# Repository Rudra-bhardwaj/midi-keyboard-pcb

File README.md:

# midi keyboard
midi keyboard is a musical synthesizer which is an electronic musical instrument that generates and modifies audio signals to create unique sounds

 ## features
1)EC11 Rotary Encoders

2)SK6812 MINI-E Neopixels

3)Bourns Slide Potentiometers

4)Kailh Choc Low-Profile Switches

5)and some copper pads to play music!

## BOM (bill of materials)
 | Designator    | Footprint                                      | Quantity | Value                    | Total Cost | Part                                                                                                                                                                                                                                                                                                                                                                                                                                                                                                                                                                                                                                                                                                |
|---------------|------------------------------------------------|----------|--------------------------|------------|-----------------------------------------------------------------------------------------------------------------------------------------------------------------------------------------------------------------------------------------------------------------------------------------------------------------------------------------------------------------------------------------------------------------------------------------------------------------------------------------------------------------------------------------------------------------------------------------------------------------------------------------------------------------------------------------------------|
| D1, D2, D3    | LED_SK6812MINI-E_3.2x2.8mm_P1.5mm_ReverseMount | 3        | SK6812MINI-E             | $3.36      | https://www.aliexpress.us/item/3256807677321116.html?spm=a2g0o.productlist.main.7.607a1c3clvX5x9&algo_pvid=bee2faba-4c6b-4fa4-89c4-5ca66e556568&algo_exp_id=bee2faba-4c6b-4fa4-89c4-5ca66e556568-6&pdp_ext_f=%7B%22order%22%3A%22643%22%2C%22eval%22%3A%221%22%2C%22fromPage%22%3A%22search%22%7D&pdp_npi=6%40dis%21CAD%215.30%214.88%21%21%213.65%213.36%21%402101e81117919481938394582e0f6e%2112000042594617264%21sea%21US%213725344934%21X%211%210%21n_tag%3A-29919%3Bd%3Ae2161723%3Bm03_new_user%3A-29895%3BpisId%3A5000000219770668&curPageLogUid=ehnx03TU7wEm&utparam-url=scene%3Asearch%7Cquery_from%3A%7Cx_object_id%3A1005007863635868%7C_p_origin_prod%3A                                 |
| J1            | Capacitive Keys                                | 1        | Capacitive Touch Buttons |            |                                                                                                                                                                                                                                                                                                                                                                                                                                                                                                                                                                                                                                                                                                     |
| RV1, RV2      | Potentiometer_Bourns_PTA1543_Single_Slide      | 2        | Slider                   | $3.16      | https://www.digikey.com/en/products/detail/bourns-inc/PTA1543-2010CIB103/3781161                                                                                                                                                                                                                                                                                                                                                                                                                                                                                                                                                                                                                    |
| SW1, SW2, SW3 | Kailh Choc Low-Profile Switches                | 3        | SW_Push                  | $6.04      | https://www.aliexpress.com/item/1005008883418065.html?spm=a2g0o.productlist.main.1.13d14a7e068OmL&algo_pvid=4e5fe6cd-3562-4ef4-ac3e-085a2d4634fe&algo_exp_id=4e5fe6cd-3562-4ef4-ac3e-085a2d4634fe-0&pdp_ext_f=%7B%22order%22%3A%221475%22%2C%22spu_best_type%22%3A%22price%22%2C%22eval%22%3A%221%22%2C%22fromPage%22%3A%22search%22%7D&pdp_npi=6%40dis%21CAD%2111.40%212.38%21%21%217.81%211.63%21%402103128917919263557114360e0ebd%2112000047082945007%21sea%21CA%210%21ABX%211%210%21n_tag%3A-29910%3Bd%3A778dde27%3Bm03_new_user%3A-29895%3BpisId%3A5000000218640848&curPageLogUid=CXjsh9TOCyFt&utparam-url=scene%3Asearch%7Cquery_from%3A%7Cx_object_id%3A1005008883418065%7C_p_origin_prod%3A |
| SW4           | RotaryEncoder_Alps_EC11E-Switch_Vertical_H20mm | 1        | RotaryEncoder_Switch_MP  | $1.44      | https://www.aliexpress.us/item/3256807457768762.html?spm=a2g0o.productlist.main.1.52d22c6as0ZCnv&algo_pvid=9965a6c7-9d4c-44f9-a2d4-a43aa1b0ae45&algo_exp_id=9965a6c7-9d4c-44f9-a2d4-a43aa1b0ae45-0&pdp_ext_f=%7B%22order%22%3A%224739%22%2C%22eval%22%3A%221%22%2C%22fromPage%22%3A%22search%22%7D&pdp_npi=6%40dis%21USD%211.52%211.40%21%21%211.52%211.40%21%402101e7a317919489056767943e0e88%2112000041630839409%21sea%21US%213725344934%21X%211%210%21n_tag%3A-29919%3Bd%3A1bb91aa6%3Bm03_new_user%3A-29895%3BpisId%3A5000000219770668&curPageLogUid=AOe3dpbqRVrY&utparam-url=scene%3Asearch%7Cquery_from%3A%7Cx_object_id%3A1005007644083514%7C_p_origin_prod%3A                                |
| U1            | Waveshare ESP32-S3-Zero                        | 1        | Waveshare ESP32-S3-ZERO  | $6.62      | https://www.aliexpress.com/item/1005007004089798.html?src=google&gatewayAdapt=4itemAdapt                                                                                                                                                                                                                                                                                                                                                                                                                                                                                                                                                                                                            |
|               |                                                |          |                          |            |                                                                                                                                                                                                                                                                                                                                                                                                                                                                                                                                                                                                                                                                                                     |
|               |                                                |          | Total Aliexpress:        | $19.59     |                                                                                                                                                                                                                                                                                                                                                                                                                                                                                                                                                                                                                                                                                                     |
|               |                                                |          | Total Digikey:           | $12.35     |                                                                                                                                                                                                                                                                                                                                                                                                                                                                                                                                                                                                                                                                                                     |
|               |                                                |          | Total JLCPCB:            | $12.29     |                                                                                                                                                                                                                                                                                                                                                                                                                                                                                                                                                                                                                                                                                                     |
|               |                                                |          | Total:                   | $44.23     |                                                                                                                                                                                                                                                                                                                                                                                                                                                                                                                                                                                                                                                                                                     |

## Images of the project

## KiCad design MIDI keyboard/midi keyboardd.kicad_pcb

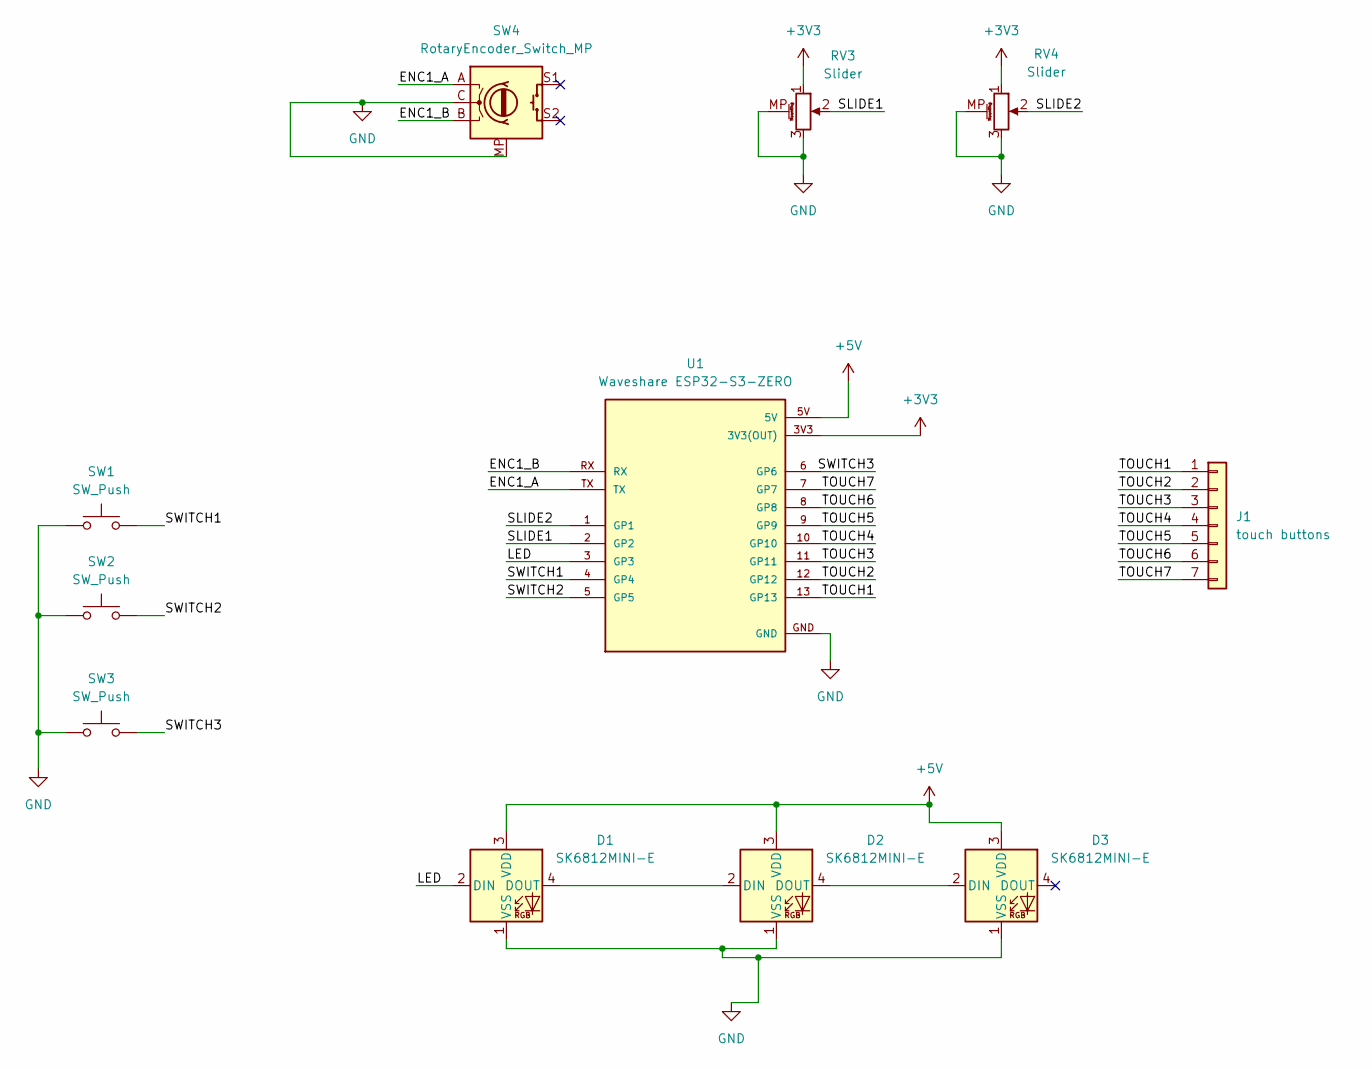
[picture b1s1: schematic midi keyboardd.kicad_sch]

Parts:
D1, D2, D3: SK6812MINI-E; LED_SK6812MINI-E_3.2x2.8mm_P1.5mm_ReverseMount
J1: touch buttons; touch pads
RV3, RV4: Slider; Potentiometer_Bourns_PTA1543_Single_Slide
SW1, SW2, SW3: SW_Push; Kailh Choc Low-Profile Switches
SW4: RotaryEncoder_Switch_MP; RotaryEncoder_Alps_EC11E-Switch_Vertical_H20mm
U1: Waveshare ESP32-S3-ZERO; Waveshare ESP32-S3-Zero; PARTREV NA

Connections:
+3V3: RV3.1, RV4.1, U1.3V3 (3V3(OUT))
+5V: D1.3 (VDD), D2.3 (VDD), D3.3 (VDD), U1.5V
/ENC1_A: SW4.A, U1.TX
/ENC1_B: SW4.B, U1.RX
/LED: D1.2 (DIN), U1.3 (GP3)
/SLIDE1: RV3.2, U1.2 (GP2)
/SLIDE2: RV4.2, U1.1 (GP1)
/SWITCH1: SW1.2, U1.4 (GP4)
/SWITCH2: SW2.2, U1.5 (GP5)
/SWITCH3: SW3.2, U1.6 (GP6)
/TOUCH1: J1.1, U1.13 (GP13)
/TOUCH2: J1.2, U1.12 (GP12)
/TOUCH3: J1.3, U1.11 (GP11)
/TOUCH4: J1.4, U1.10 (GP10)
/TOUCH5: J1.5, U1.9 (GP9)
/TOUCH6: J1.6, U1.8 (GP8)
/TOUCH7: J1.7, U1.7 (GP7)
GND: D1.1 (VSS), D2.1 (VSS), D3.1 (VSS), RV3.3, RV3.MP (MountPin), RV4.3, RV4.MP (MountPin), SW1.1, SW2.1, SW3.1, SW4.C, SW4.MP, U1.GND
unnamed: D1.4 (DOUT), D2.2 (DIN)
unnamed: D2.4 (DOUT), D3.2 (DIN)

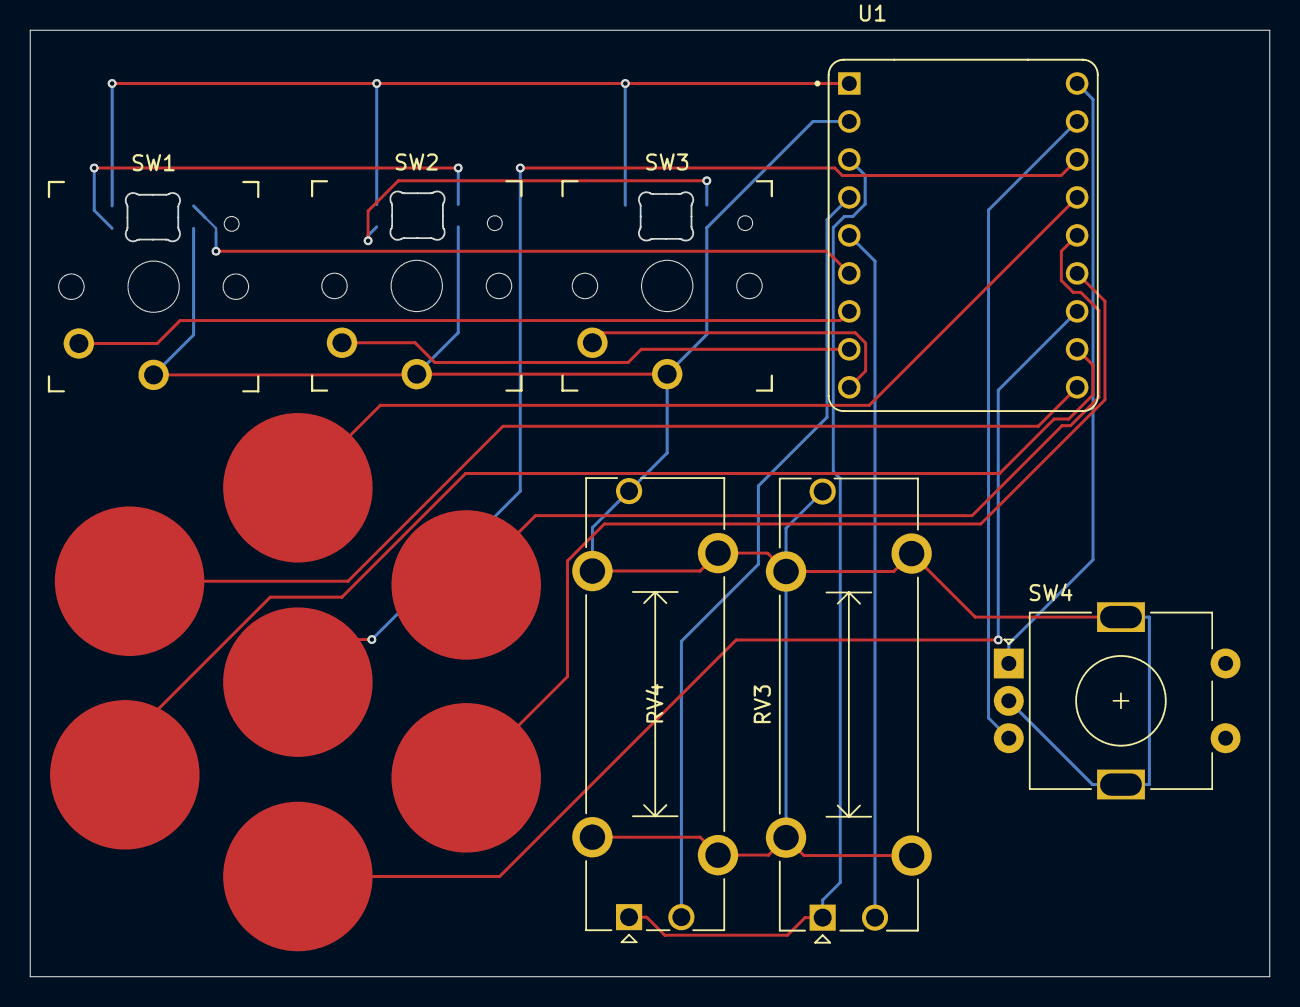
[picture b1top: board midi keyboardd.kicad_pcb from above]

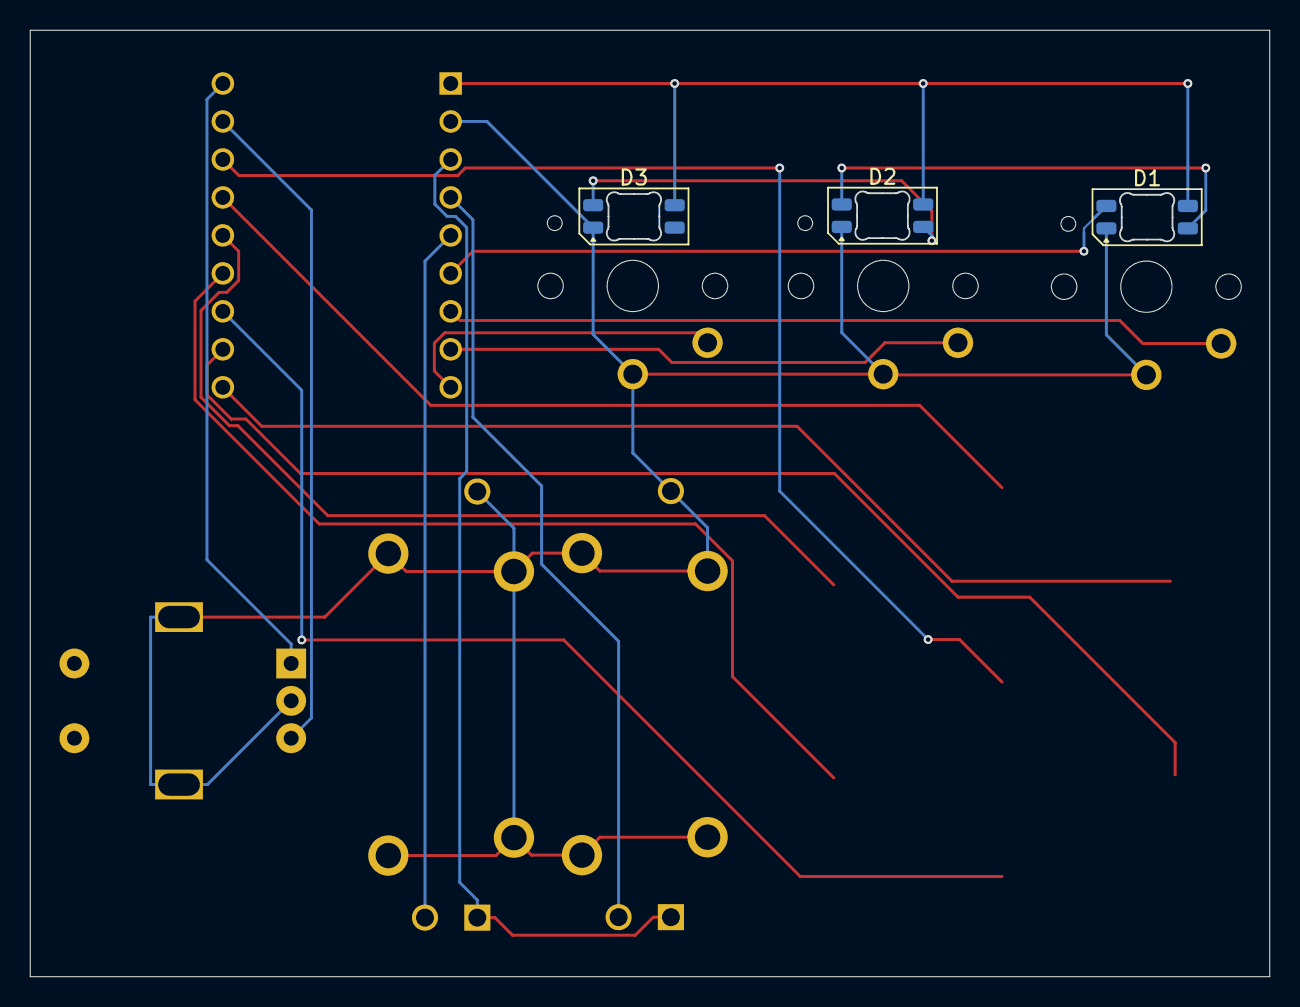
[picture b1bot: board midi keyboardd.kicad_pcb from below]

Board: 2 copper layers, 82.9 x 63.3 mm, 11 parts (3 on the bottom side), 20 nets.
